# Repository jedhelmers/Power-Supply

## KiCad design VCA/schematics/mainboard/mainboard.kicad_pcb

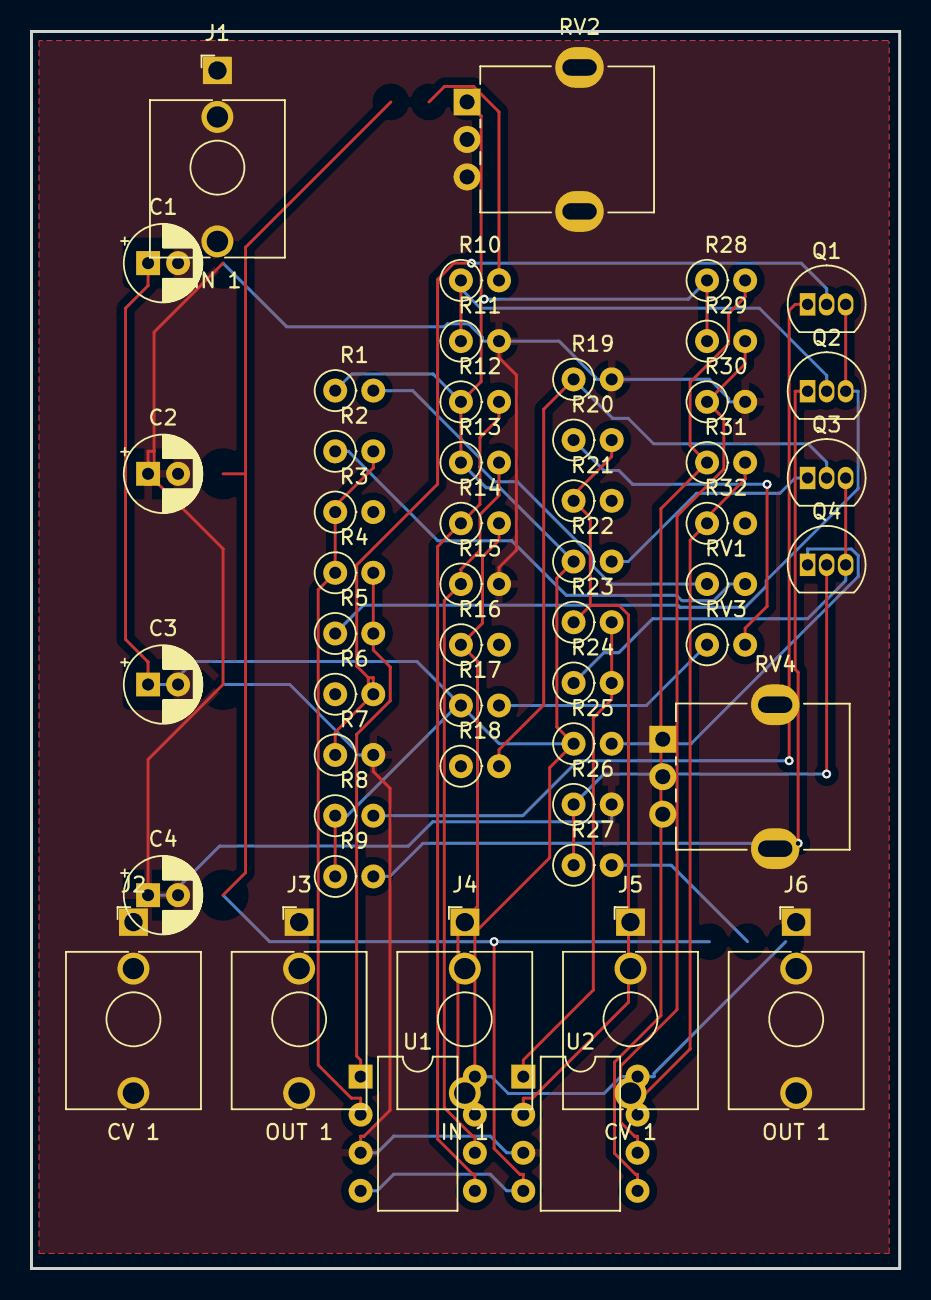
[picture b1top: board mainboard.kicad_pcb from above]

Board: 2 copper layers, 57.9 x 82.5 mm, 52 parts (0 on the bottom side), 35 nets.

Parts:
C1, C2, C3, C4: 0.1uF; CP_Radial_D5.0mm_P2.00mm
J1, J4: IN 1; AudioJack_3.5mm
J2, J5: CV 1; AudioJack_3.5mm
J3, J6: OUT 1; AudioJack_3.5mm
Q1, Q2, Q3, Q4: BC548; TO-92_Inline
R1, R8, R9, R17, R22, R25: 20k; R_Axial_DIN0207_L6.3mm_D2.5mm_P2.54mm_Vertical
R2, R3, R6, R14, R15, R18, R20, R21, R30, R31: 100k; R_Axial_DIN0207_L6.3mm_D2.5mm_P2.54mm_Vertical
R4, R23: 82k; R_Axial_DIN0207_L6.3mm_D2.5mm_P2.54mm_Vertical
R5, R12, R13, R24, R28, R29: 10k; R_Axial_DIN0207_L6.3mm_D2.5mm_P2.54mm_Vertical
R7, R19: 100; R_Axial_DIN0207_L6.3mm_D2.5mm_P2.54mm_Vertical
R10, R11, R26, R27: R; R_Axial_DIN0207_L6.3mm_D2.5mm_P2.54mm_Vertical
R16, R32: 1k; R_Axial_DIN0207_L6.3mm_D2.5mm_P2.54mm_Vertical
RV1, RV3: 100k; R_Axial_DIN0207_L6.3mm_D2.5mm_P2.54mm_Vertical
RV2, RV4: R_Potentiometer; Potentiometer_RV09
U1, U2: TL072; DIP-8_W7.62mm

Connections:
GND: C1.2, C2.1, C3.2, C4.1, J1.S, J2.S, J3.S, J4.S, J5.S, J6.S, R7.2, R11.2, R15.2, R19.2, R26.2, R30.2, U1.3 (+), U2.3 (+)
unnamed: J1.T, R6.1
unnamed: J2.T, R3.2
unnamed: J3.T, R16.2
unnamed: J4.T, R18.1
unnamed: J5.T, R21.2
unnamed: J6.T, R32.2
unnamed: Q1.2 (B), R6.2, R7.1
unnamed: Q1.1 (C), R8.2
unnamed: Q1.3 (E), Q2.3 (E), R5.1
unnamed: Q2.2 (B), R10.1, R11.1
unnamed: Q2.1 (C), R9.2
unnamed: Q3.2 (B), R18.2, R19.1
unnamed: Q3.1 (C), R22.2
unnamed: Q3.3 (E), Q4.3 (E), R24.1
unnamed: Q4.2 (B), R26.1, R27.1
unnamed: Q4.1 (C), R25.2
unnamed: R1.2, RV1.1
unnamed: R2.1, RV1.2
unnamed: R4.2, R5.2, U1.1
unnamed: R10.2, RV2.2
unnamed: R14.2, R16.1, U1.7
unnamed: R17.2, RV3.1
unnamed: R20.1, RV3.2
unnamed: R23.2, R24.2, U2.1
unnamed: R27.2, RV4.2
unnamed: R31.2, R32.1, U2.7
unnamed: R2.2, R3.1, R4.1, U1.2 (-)
unnamed: R12.2, R14.1, U1.5 (+)
unnamed: R13.2, R15.1, U1.6 (-)
unnamed: R20.2, R21.1, R23.1, U2.2 (-)
unnamed: R28.2, R31.1, U2.5 (+)
unnamed: R29.2, R30.1, U2.6 (-)
VCC: C1.1, C3.1, R1.1, R8.1, R9.1, R12.1, R13.1, R17.1, R22.1, R25.1, R28.1, R29.1, RV2.1, RV4.1, U1.8 (V+), U2.8 (V+)
VEE: C2.2, C4.2, RV2.3, RV4.3, U1.4 (V-), U2.4 (V-)

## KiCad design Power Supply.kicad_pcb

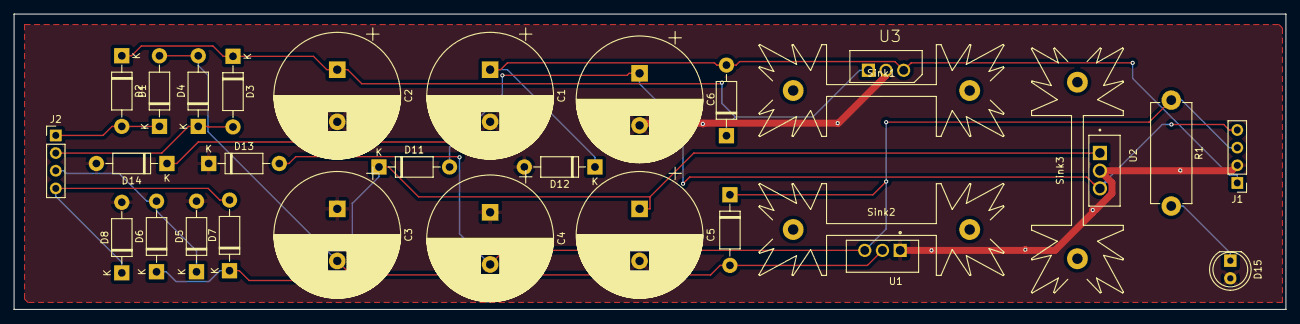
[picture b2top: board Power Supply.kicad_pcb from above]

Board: 2 copper layers, 183.0 x 42.5 mm, 30 parts (0 on the bottom side), 12 nets.

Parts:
C1, C4, C6: 10uF; CP_Radial_D18.0mm_P7.50mm
C2, C3: 1000uF; CP_Radial_D18.0mm_P7.50mm
C5: 2200uF; CP_Radial_D18.0mm_P7.50mm
D1, D2, D3, D4, D5, D6, D7, D8, D9, D10, D11, D12, D13, D14: 1N4002; D_DO-41_SOD81_P10.16mm_Horizontal
D15: LED; LED_D5.0mm
J1, J2: Conn_01x04_Socket; PinHeader_1x04_P2.54mm_Vertical
R1: 1k5; R_Axial_DIN0614_L14.3mm_D5.7mm_P15.24mm_Horizontal
Sink1, Sink2, Sink3: Heatsink_Fischer_SK104-STCB_35x13mm__2xDrill1.5mm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; Heatsink_Fischer_SK104-STCB_35x13mm__2xDrill1.5mm_ScrewM3
U1: L7915; L7915CV TO255P1040X460X1935-3
U2: L7805; L7805 TO255P1020X450X2000-3
U3: L7815; L7815CV TO254P450X1020X1935-3P

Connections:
GND: C1.2, C2.2, C3.1, C4.1, C5.2, C6.2, D5.2 (A), D8.2 (A), D12.2 (A), D13.1 (K), D14.2 (A), D15.2 (A), J1.2, U1.1 (GND), U2.2 (GND), U3.2 (GND)
unnamed: C3.2, D1.2 (A), D4.2 (A), D10.2 (A), U1.2 (VI)
unnamed: D1.1 (K), D2.2 (A), J2.1
unnamed: C2.1, D2.1 (K), D3.1 (K), D9.1 (K), U3.1 (IN)
unnamed: D3.2 (A), D4.1 (K), J2.2
unnamed: D5.1 (K), D6.2 (A), J2.3
unnamed: D7.2 (A), D8.1 (K), J2.4
unnamed: C4.2, D10.1 (K), D13.2 (A), J1.3, R1.1, U1.3 (VO)
unnamed: C6.1, D11.2 (A), D14.1 (K), J1.4, U2.3 (OUT)
unnamed: C5.1, D6.1 (K), D7.1 (K), D11.1 (K), U2.1 (IN)
unnamed: C1.1, D9.2 (A), D12.1 (K), J1.1, U3.3 (OUT)
unnamed: D15.1 (K), R1.2

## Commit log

2024-12-05 init
2024-12-06 uodates
2024-12-13 stuff
